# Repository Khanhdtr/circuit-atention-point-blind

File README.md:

# circuit-atention-point-blind
Mạch cảnh báo điểm mù
## Yêu cầu thiết kế
-Nguồn vào 24V DC dùng MC24063 => 5V
- IC dùng STM8S0003F3
- Đọc cảnh báo Ultrasonic ( JSN-SR04T)
- Giao tiếp về trung tâm qua đường RS485
## Tổng quan
### Sơ đồ nguyên lý

### PCB

### 3D

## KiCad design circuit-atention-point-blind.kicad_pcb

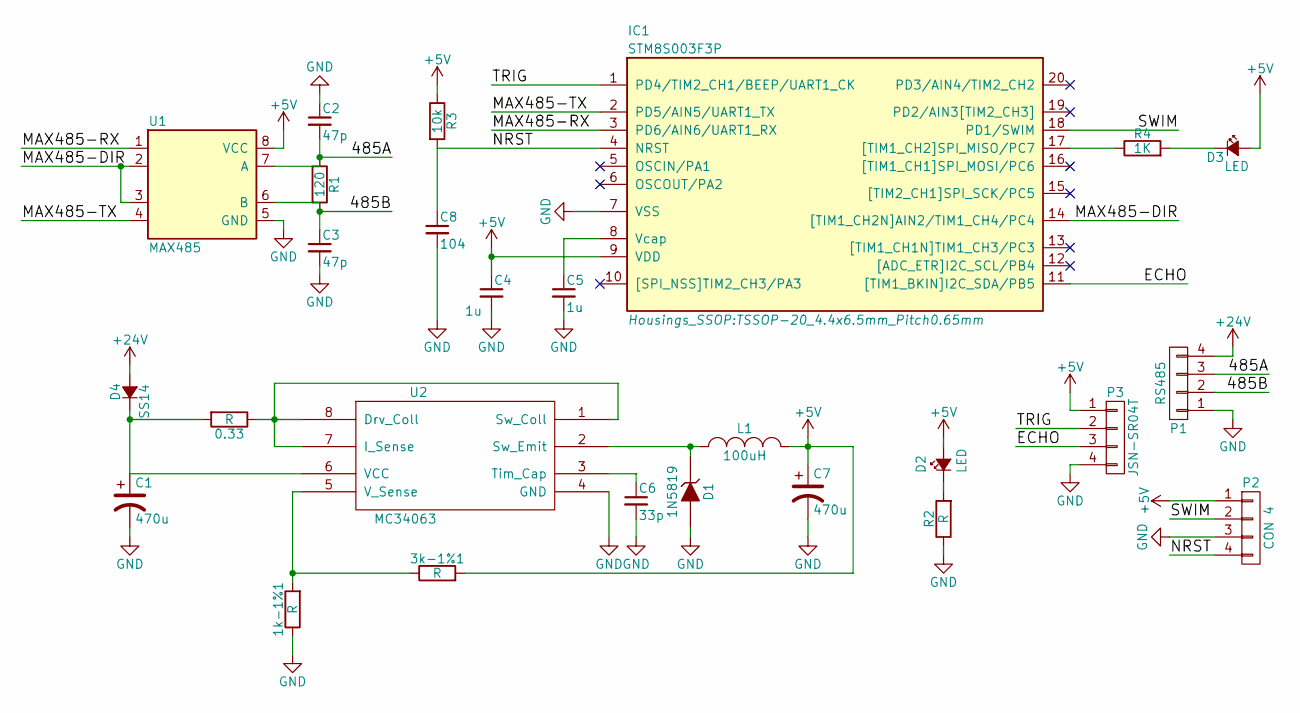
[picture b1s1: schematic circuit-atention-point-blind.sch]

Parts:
0.33, 1k-1%1, 3k-1%1: R; R_0805_HandSoldering
C1: 470u; c_elec_10x10
C2, C3: 47p; C_0805_HandSoldering
C4, C5: 1u; C_0805_HandSoldering
C6: 33p; C_0805_HandSoldering
C7: 470u; c_elec_6.3x5.7
C8: 104; C_0805_HandSoldering
D1: 1N5819; MELF_Standard
D2, D3: LED; LED_0805
D4: SS14; DO-214BA
IC1: STM8S003F3P; TSSOP-20_4.4x6.5mm_Pitch0.65mm
L1: 100uH; Neosid_Inductor_SM1206
P1: RS485; Molex_KK_6410-04
P2: CON 4; Pin_Header_Angled_1x04
P3: JSN-SR04T; Pin_Header_Angled_1x04
R1: 120; R_0805_HandSoldering
R2: R; R_0805_HandSoldering
R3: 10k; R_0805_HandSoldering
R4: 1K; R_0805_HandSoldering
U1: MAX485; SOIC-8_3.9x4.9mm_Pitch1.27mm
U2: MC34063; SOIC-8_3.9x4.9mm_Pitch1.27mm

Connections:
+5V: 3k-1%1.2, C4.1, C7.1, D2.2 (A), D3.2 (A), IC1.9 (VDD), L1.2, P2.1, P3.1, R3.1, U1.8 (VCC)
+24V: D4.2 (A), P1.4
/485A: C2.2, P1.3, R1.1, U1.7 (A)
/485B: C3.1, P1.2, R1.2, U1.6 (B)
/ECHO: IC1.11 ([TIM1_BKIN]I2C_SDA/PB5), P3.3
/MAX485-DIR: IC1.14 ([TIM1_CH2N]AIN2/TIM1_CH4/PC4), U1.2, U1.3
/MAX485-RX: IC1.3 (PD6/AIN6/UART1_RX), U1.1
/MAX485-TX: IC1.2 (PD5/AIN5/UART1_TX), U1.4
/NRST: C8.1, IC1.4 (NRST), P2.4, R3.2
/SWIM: IC1.18 (PD1/SWIM), P2.2
/TRIG: IC1.1 (PD4/TIM2_CH1/BEEP/UART1_CK), P3.2
GND: 1k-1%1.1, C1.2, C2.1, C3.2, C4.2, C5.2, C6.2, C7.2, C8.2, D1.2 (A), IC1.7 (VSS), P1.1, P2.3, P3.4, R2.1, U1.5 (GND), U2.4 (GND)
unnamed: 0.33.1, U2.1 (Sw_Coll), U2.7 (I_Sense), U2.8 (Drv_Coll)
unnamed: 0.33.2, C1.1, D4.1 (K), U2.6 (VCC)
unnamed: 1k-1%1.2, 3k-1%1.1, U2.5 (V_Sense)
unnamed: C5.1, IC1.8 (Vcap)
unnamed: C6.1, U2.3 (Tim_Cap)
unnamed: D1.1 (K), L1.1, U2.2 (Sw_Emit)
unnamed: D2.1 (K), R2.2
unnamed: D3.1 (K), R4.2
unnamed: IC1.17 ([TIM1_CH2]SPI_MISO/PC7), R4.1

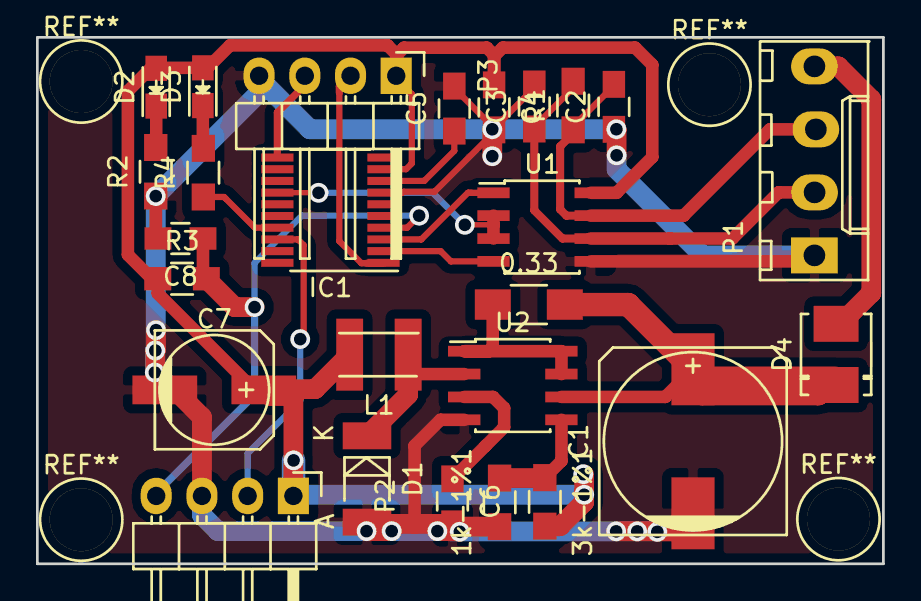
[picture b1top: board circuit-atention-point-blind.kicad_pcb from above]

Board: 2 copper layers, 47.0 x 29.2 mm, 26 parts (0 on the bottom side), 21 nets.

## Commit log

2016-07-02 init circuit warning point blind
2016-07-02 modify sch
2016-07-02 initial PCB
2016-07-02 backup PCB after modify 1st
2016-07-02 backup PCB after modify 2nd
2016-07-05 backup PCB after modify 3nd
2016-07-05 finish pcb (version1)
